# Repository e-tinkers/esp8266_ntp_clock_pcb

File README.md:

## ESP8266 NTP Clock

This is the kicad v5.x hardware design file for the ESP8266 NTP Clock with Charlieplexing technique described on my web post [ESP8266 NTP Clock with NTP upate and Charlieplexing]( https://www.e-tinkers.com/2022/04/esp8266-ntp-clock-with-ntp-update-and-charlieplexing/).

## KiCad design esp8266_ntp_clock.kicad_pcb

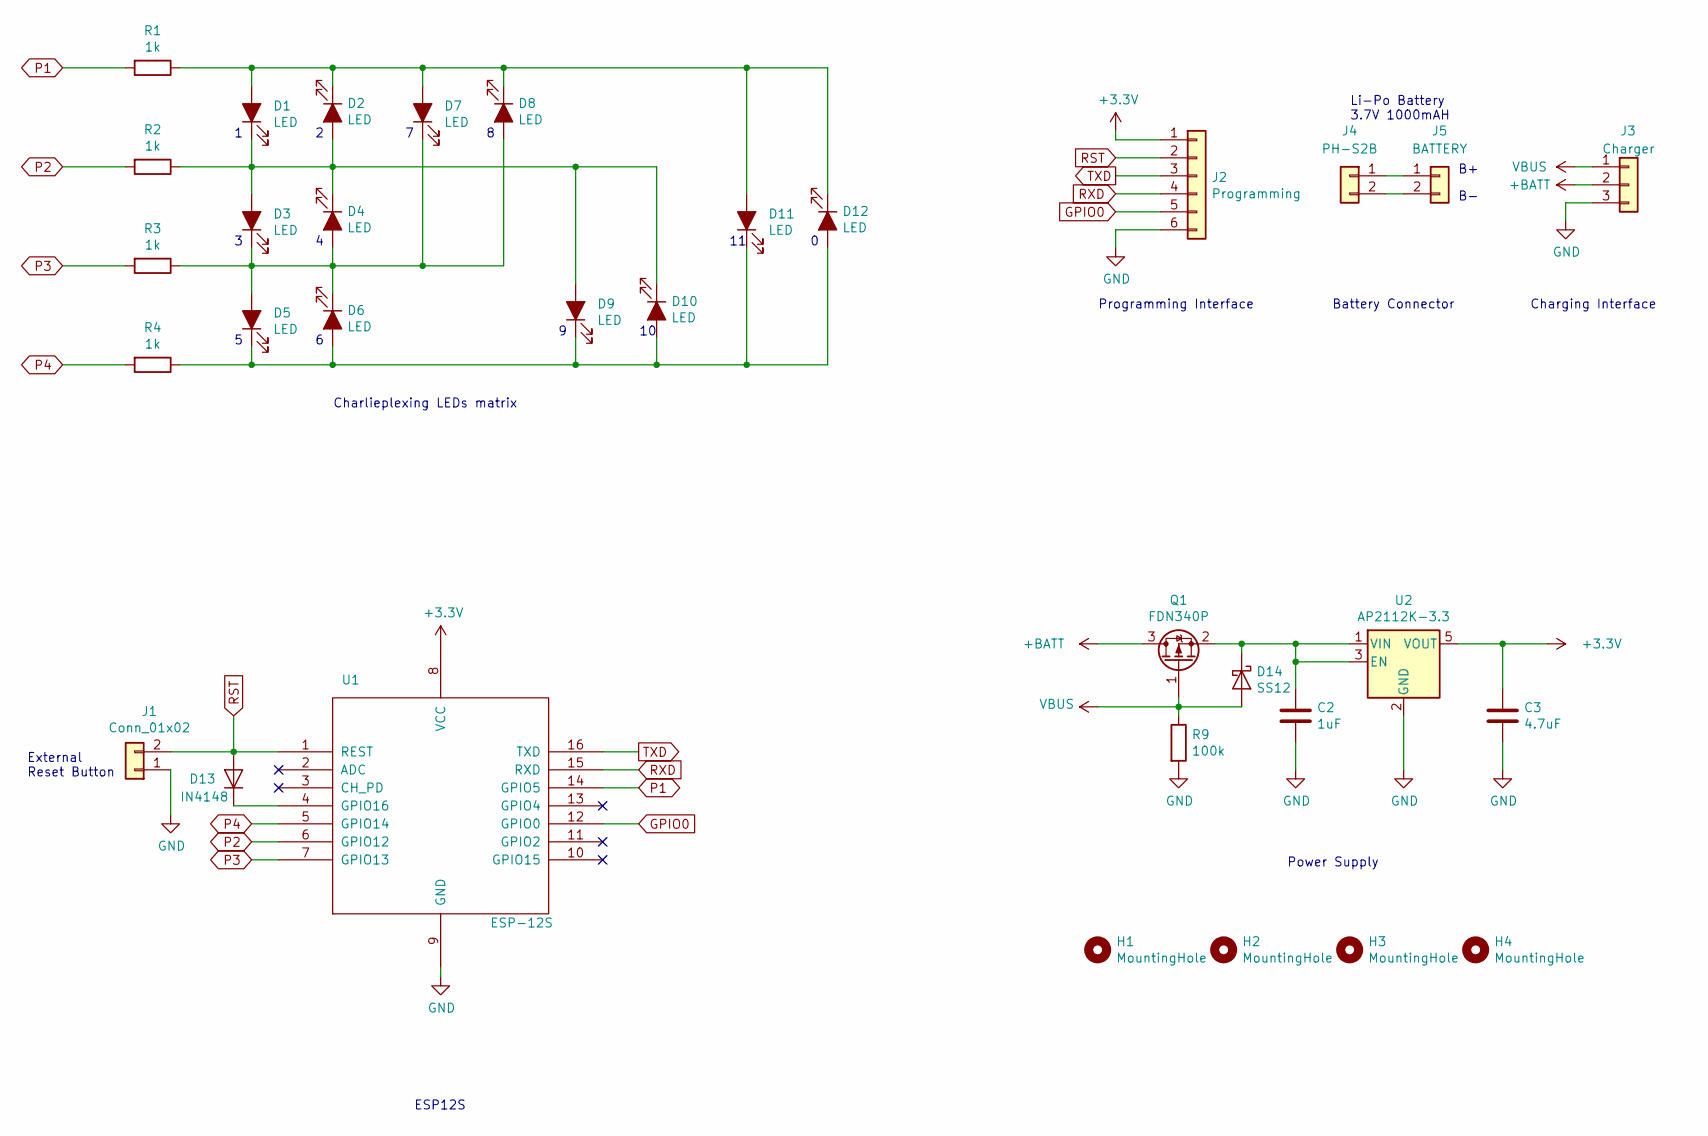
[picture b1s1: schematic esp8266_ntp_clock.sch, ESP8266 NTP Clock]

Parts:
C2: 1uF; C_0603_1608Metric_Pad1.05x0.95mm_HandSolder
C3: 4.7uF; C_0603_1608Metric_Pad1.05x0.95mm_HandSolder
D1, D2, D3, D4, D5, D6, D7, D8, D9, D10, D11, D12: LED; LED_D3.0mm
D13: IN4148; D_SOD-123
D14: SS12; D_SMA_Handsoldering
H1, H2, H3, H4: MountingHole; MountingHole_4.5mm_Pad
J1: Conn_01x02; PinHeader_1x02_P2.54mm_Vertical
J2: Programming; PinHeader_1x06_P2.54mm_Vertical
J3: Charger; PinHeader_1x03_P2.54mm_Vertical
J4: PH-S2B; JST_PH_S2B-PH-K_1x02_P2.00mm_Horizontal
J5: BATTERY; PinHeader_1x02_P2.54mm_Vertical
Q1: FDN340P; SOT-23_Handsoldering
R1, R2, R3, R4: 1k; R_0603_1608Metric_Pad1.05x0.95mm_HandSolder
R9: 100k; R_0805_2012Metric_Pad1.15x1.40mm_HandSolder
U1: ESP-12S
U2: AP2112K-3.3; SOT-23-5_HandSoldering

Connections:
+3V3: C3.1, J2.1, U1.8 (VCC), U2.5 (VOUT)
+BATT: J3.2, Q1.3 (D)
GND: C2.2, C3.2, J1.1, J2.6, J3.3, R9.2, U1.9 (GND), U2.2 (GND)
GPIO0: J2.5, U1.12 (GPIO0)
unnamed: C2.1, D14.1 (K), Q1.2 (S), U2.1 (VIN), U2.3 (EN)
unnamed: D1.1 (K), D2.2 (A), D3.2 (A), D4.1 (K), D9.2 (A), D10.1 (K), R2.1
unnamed: D1.2 (A), D2.1 (K), D7.2 (A), D8.1 (K), D11.2 (A), D12.1 (K), R1.1
unnamed: D3.1 (K), D4.2 (A), D5.2 (A), D6.1 (K), D7.1 (K), D8.2 (A), R3.1
unnamed: D5.1 (K), D6.2 (A), D9.1 (K), D10.2 (A), D11.1 (K), D12.2 (A), R4.1
unnamed: D13.1 (K), U1.4 (GPIO16)
unnamed: J4.1, J5.1
unnamed: J4.2, J5.2
P1: R1.2, U1.14 (GPIO5)
P2: R2.2, U1.6 (GPIO12)
P3: R3.2, U1.7 (GPIO13)
P4: R4.2, U1.5 (GPIO14)
RST: D13.2 (A), J1.2, J2.2, U1.1 (REST)
RXD: J2.4, U1.15 (RXD)
TXD: J2.3, U1.16 (TXD)
VBUS: D14.2 (A), J3.1, Q1.1 (G), R9.1

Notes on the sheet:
Charlieplexing LEDs matrix
ESP12S
Power Supply
Li-Po Battery 3.7V 1000mAH
Programming Interface
External Reset Button
Battery Connector
Charging Interface

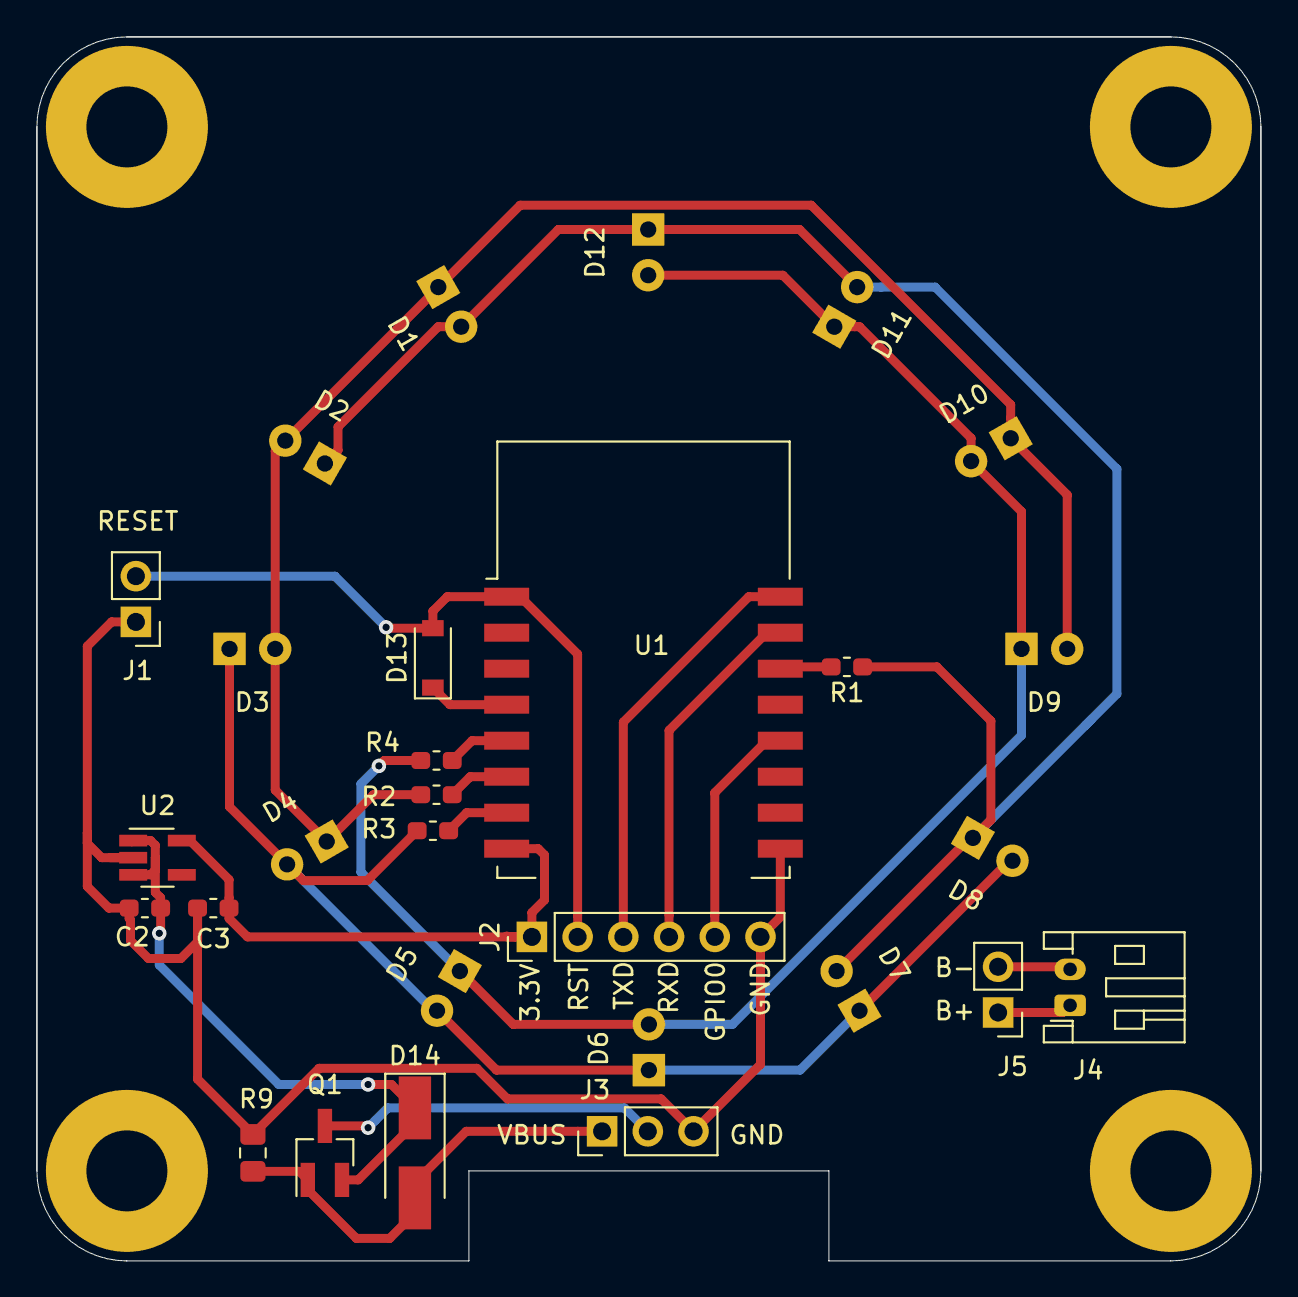
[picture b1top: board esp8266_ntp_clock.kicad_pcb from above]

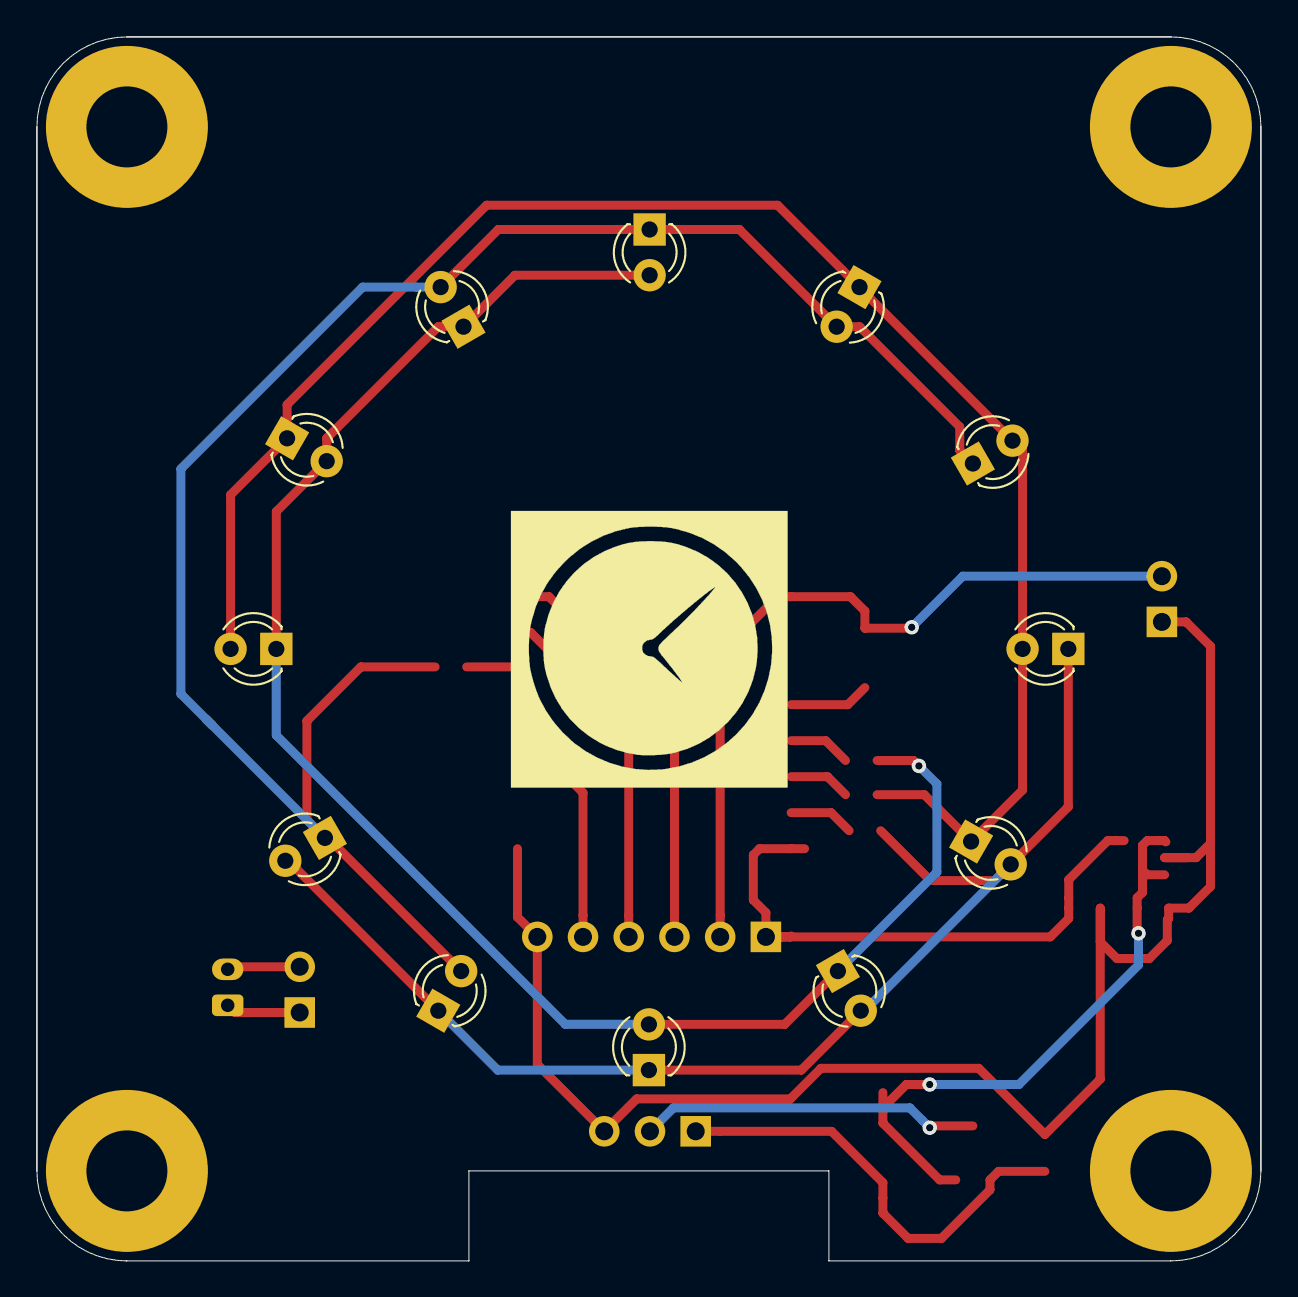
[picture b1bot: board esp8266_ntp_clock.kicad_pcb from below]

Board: 2 copper layers, 68.0 x 68.0 mm, 33 parts (12 on the bottom side), 20 nets.

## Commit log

2024-01-06 component replacements for reducing quiescent current
